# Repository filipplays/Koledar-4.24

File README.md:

# Koledar 4.24 <br /> _The customizable birthday calendar_

---

This is my attempt at making a simple calendar for the elderly. It displays the date, time, and up to three birthdays at a time. It was made with the intention that a caretaker would input up to 146 birthdays to the Koledar hardware with the Koledar GUI and take the device to the person's home, where it just needs to be powered next to a window.
<br/> The device uses GPS to read the date and time which makes it completely autonomous.
<br/> The project was made to help my grandma stay as independent as possible by helping her with attending appointments, watching TV shows, and remembering birthdays. It took some getting used to but she says that it is helpful.
<br/> The project started as an extra assignment in the first year of my bachelor's degree in electrical engineering, and it has now been updated two times.

## The creation of the project

### Hardware

The only thing I designed myself was the connector PCB. It neatly fits into the casing and connects the GPS module, display, and Arduino.

I used the [NEO-6M GPS module](https://randomnerdtutorials.com/guide-to-neo-6m-gps-module-with-arduino/) for connectivity because it is very well supported on Arduino. The screen is a [5'' touch screen from DIY more](https://www.diymore.cc/products/5-0-800x480-tft-lcd-module-display-touch-panel-ssd1963-for-51-avr-stm32/) with a resolution of 800x480px. I know which library to use with it since I have used it in the previous version and I didn't have any problems with it, so I just used it again. [This](http://rinkydinkelectronics.com/library.php?id=51) is the LCD library. I used a knockoff [Arduino MEGA 2560](https://store.arduino.cc/en-si/products/arduino-mega-2560-rev3?srsltid=AfmBOopCFWO4uVFIkQQ2IXemMtiKCIKrwHhKWaTtJ1ZzTIYdNrtdq98T) board. I didn't put a lot of thought into the board selection. I used an Arduino for all of the previous versions and since the only necessity was enough pins to drive the display and communicate with the GPS module, and the MCU didn't have to be fast or feature-rich, I stuck with the Arduino. For the next iteration, I will consider other platforms.
<br> Altogether the hardware for the latest version costs approx. 70€, and it was all bought from AliExpress.

### Case

The wooden case was made by my [dad](https://www.instagram.com/bybojci/). He used a laser cutter and thin pieces of wood to complete the construction. Since we only made a couple of these systems we made sure that the final product looked and felt pleasing.

### Firmware

I wrote all of the firmware excluding the LCD and GPS libraries and the code in the "byDay_of_week" function. That code was taken from the internet in my first year but I can't find the source.
<br/> The emphasis when writing the FW was readability and maintainability. I decided to try to use a version of the Hungarian notation, commented all of the code in Doxy style, and used it to generate the documentation. I found the style pleasant but unnecessary at times. I feel like the Doxygen-generated documentation will be useful when coming back to the project at a later time.

<center></center>

<br/> The FW needs to handle getting the time and date from GPS and displaying the appropriate data. When the GUI connects to the HW over USB it also needs to handle the communication, writing, and reading from the EEPROM. In the case that the GPS signal is lost the system displays small text in the bottom left corner indicating that the date and time functionality is being powered from the internal Arduino clock. This is not ideal as the timer is not accurate at all, but for a short time while the GPS signal is not available it's fine.
<br/> The screen used to go black during the night but it was still somewhat bright because of the backlight. I scratched the trace used for powering the LCD backlight in half and sodered a transistor I had in between the connections. I used a free Arduino PWM-enabled GPIO to drive the LCD brightness which enabled me to completely turn it off or dim it.
<br/> The fonts from the [LCD library](http://rinkydinkelectronics.com/library.php?id=51) didn't work well for me so I decided to make my own. I made a simple website that enabled me to draw the letters in a 10 by 12 grid and copy the unsigned integer array to put into a header file. This way I could quickly iterate over different designs and add Slovenian characters that aren't in the English alphabet.

<center>

</center>

## GUI

<center>

</center>

I wanted anyone to be able to set up the Koledar so I made the Koledar GUI. It is a Windows application written in Python using Tkinter. Its main functionality is to enable the user to read and write birthdays to the system, but it can also change the text and background color and change the default brightness of the screen.
<br/> The improvement from the previous version was focused on the user experience. I added an alert box when the user attempts to delete the birthdays and the theme profile. I also changed the button layout in a way that makes more sense.

<center>

</center>

## Known issues

- With certain combinations of colors and brightness the screen starts displaying an effect similar to when a screen is recorded and the shutters aren't in sync.
- The upload of all 146 birthdays takes approx. 15 seconds. At this time the Koledar GUI is unresponsive.
- The user is unable to write the letter 'č' in the Koledar GUI, so they have to copy it from another editor and paste it in.
- Birthdays with names longer than ~19 characters (depending on the birthday date) are very small on the display.

## Future Improvements

The main feature I would change is the way in which the system tracks the time. I initially chose GPS when the system didn't have the ability to store and display birthdays because I wanted it to be plug-and-play. Meaning that I just brought it to where I wanted it (and near a window) and powered it. It also meant that anytime the system was reset it didn't need any input from the user.
<br> For future versions I would use an accurate RTC IC with a coin battery backup, like [this](https://eu.mouser.com/ProductDetail/NXP-Semiconductors/PCF2131TFY?qs=QNEnbhJQKvbnVL67jlWDOg%3D%3D). Since the user needs to upload the birthdays the system needs to be connected to a PC at least once, where it could read the date and time or let the user input their own. These systems also take care of the calendar logic. This would have the advantage of not having to place the Koledar next to a window, and once it was in sync it wouldn't have to wait for any signal if it was reset.
<br> I could also make use of the longwave time signal stations like [DCF77](https://en.wikipedia.org/wiki/DCF77). This could be used for a separate system that doesn't need the birthday functionality so it would never get connected to a PC to set the time.

<br> Another interesting thing to change would be the MCU. In this context, I think there is nothing wrong with using an Arduino, but using something like an ESP32 devkit or a custom PCB could be interesting for the connectivity. I'm just not sure what I would use it for... yet!

<br> The screen was the most expensive part of the build and I think I can do the build for cheaper. It's nice that it is a touch-capable display so that when the screen is turned off you can briefly turn it on when you touch it, but I could also add a small button to the case for that, and maybe other controls as well. It might also make for a good tactile addition.

<br> I might do an E-INK, battery-powered, cordless Koledar at some point too.

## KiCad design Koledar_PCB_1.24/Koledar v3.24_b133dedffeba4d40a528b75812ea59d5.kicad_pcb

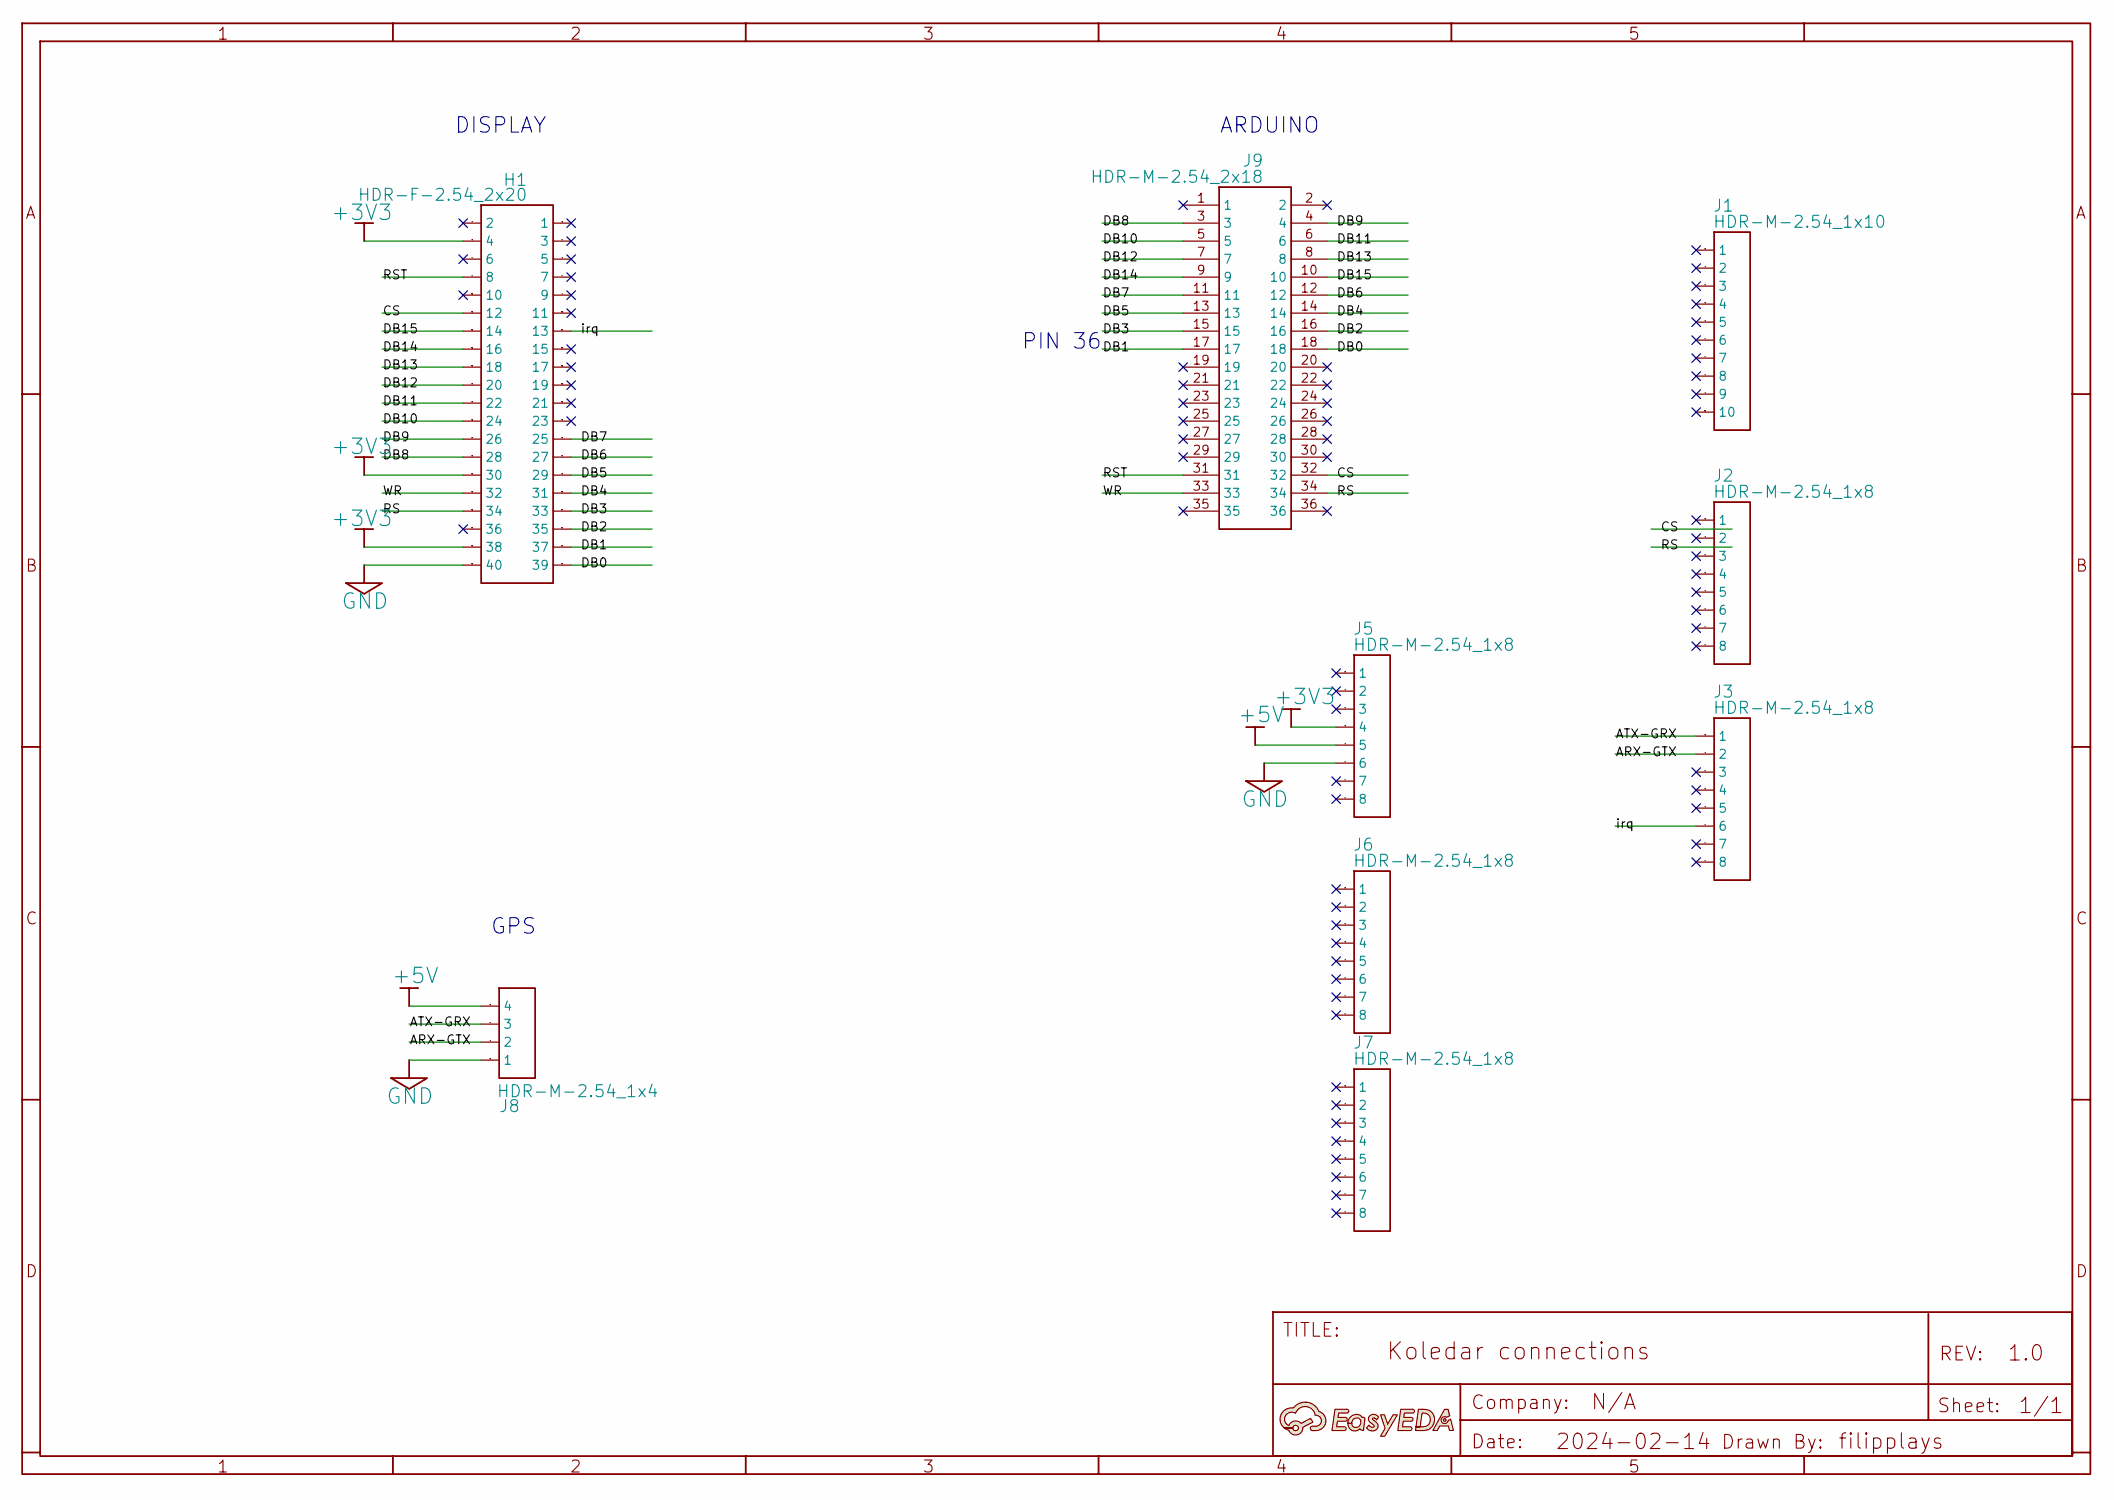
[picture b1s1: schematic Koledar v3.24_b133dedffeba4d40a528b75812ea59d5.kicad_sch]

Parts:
A: A; Manufacturer Part ?
H1: HDR-F-2.54_2x20
J1: HDR-M-2.54_1x10
J2, J3, J5, J6, J7: HDR-M-2.54_1x8
J8: HDR-M-2.54_1x4
J9: HDR-M-2.54_2x18

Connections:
+3V3: H1.4, H1.30, H1.38, J5.4
+5V: J5.5, J8.4
ARX-GTX: J3.2, J8.2
ATX-GRX: J3.1, J8.3
CS: H1.12, J9.32
DB0: H1.39, J9.18
DB1: H1.37, J9.17
DB2: H1.35, J9.16
DB3: H1.33, J9.15
DB4: H1.31, J9.14
DB5: H1.29, J9.13
DB6: H1.27, J9.12
DB7: H1.25, J9.11
DB8: H1.28, J9.3
DB9: H1.26, J9.4
DB10: H1.24, J9.5
DB11: H1.22, J9.6
DB12: H1.20, J9.7
DB13: H1.18, J9.8
DB14: H1.16, J9.9
DB15: H1.14, J9.10
GND: H1.40, J5.6, J8.1
IRQ: H1.13, J3.6
RS: H1.34, J9.34
RST: H1.8, J9.31
WR: H1.32, J9.33

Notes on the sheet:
DISPLAY
ARDUINO
PIN 36
GPS

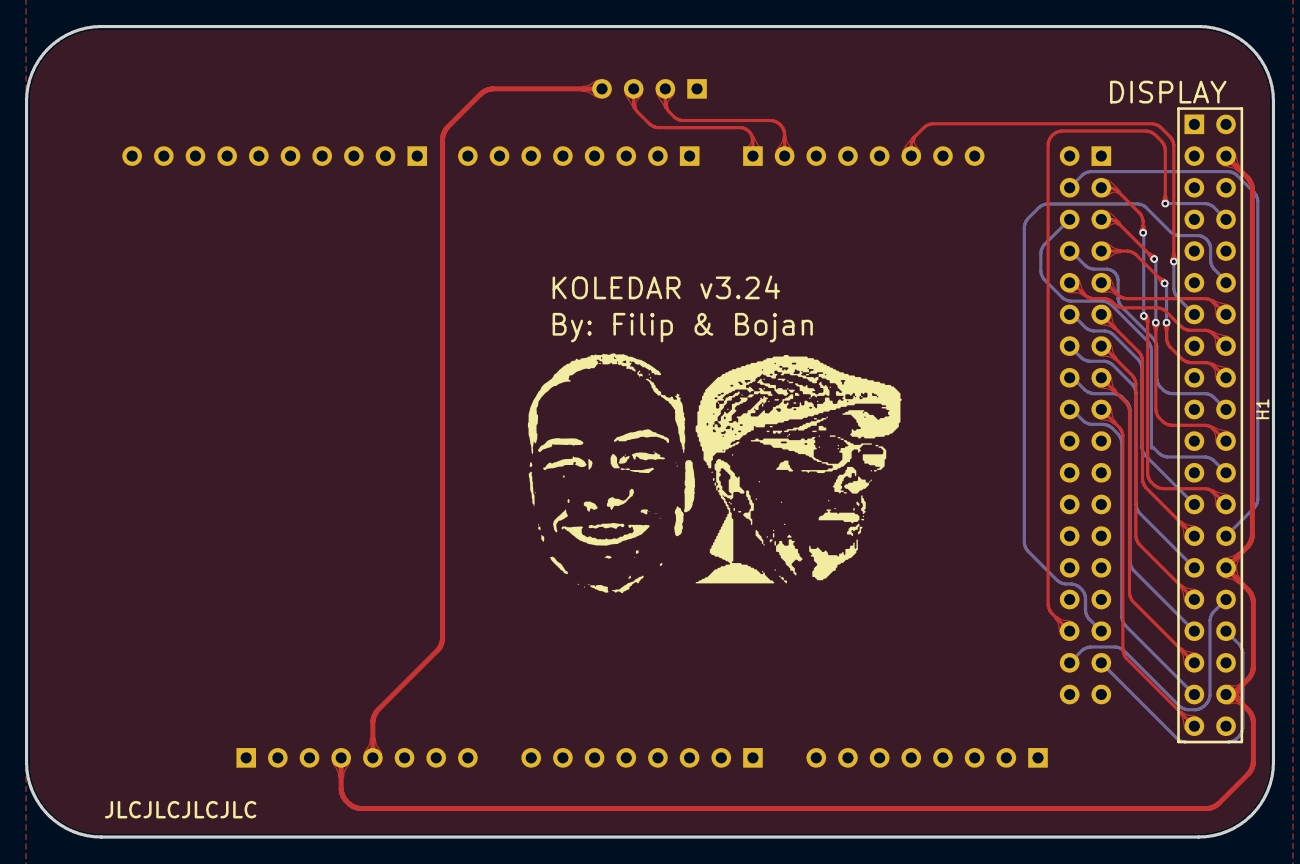
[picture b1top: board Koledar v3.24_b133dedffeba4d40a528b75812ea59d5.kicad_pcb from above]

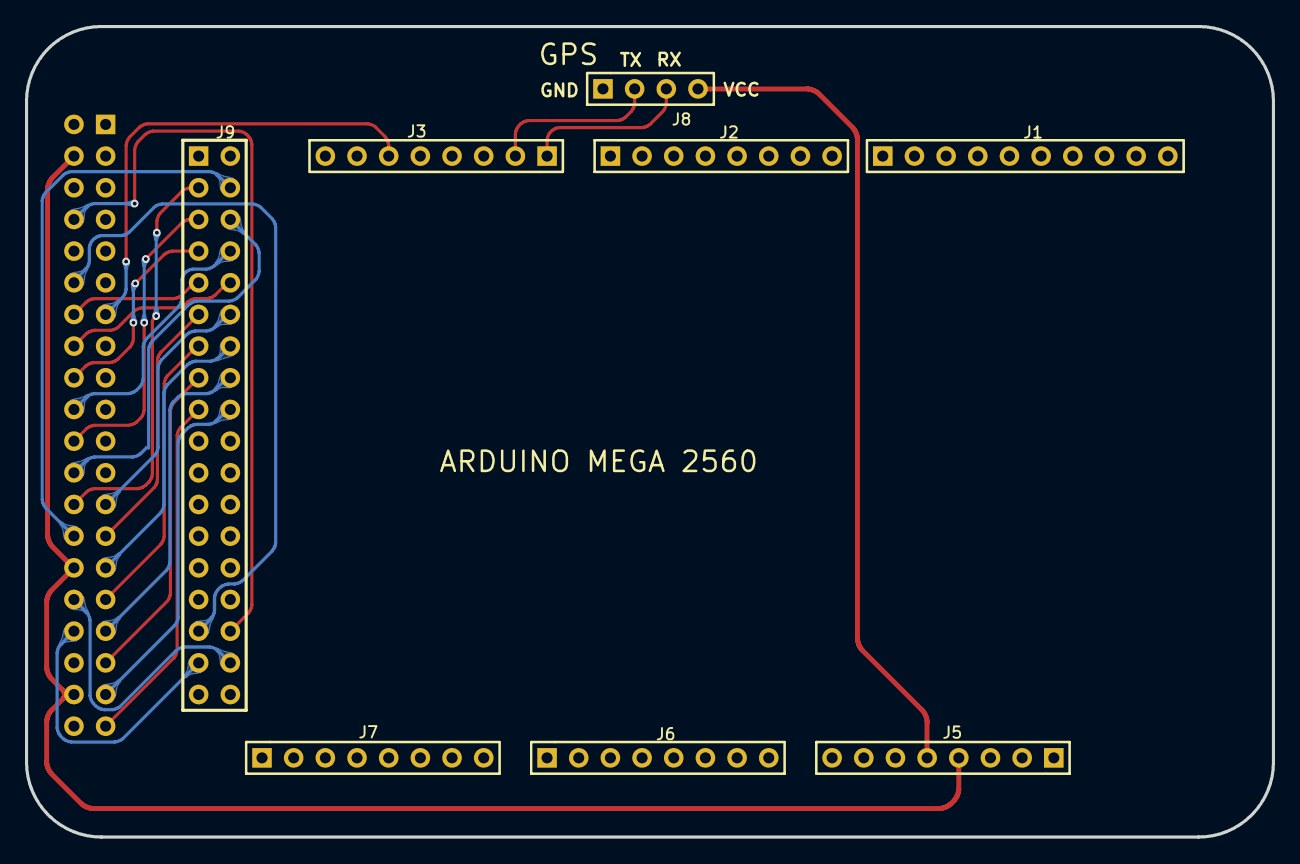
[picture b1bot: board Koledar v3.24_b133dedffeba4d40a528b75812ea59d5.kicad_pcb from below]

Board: 2 copper layers, 100.0 x 65.0 mm, 9 parts (8 on the bottom side), 26 nets.

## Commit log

2024-10-16 REAME and repo languages FIX
2025-01-25 Bug fix and code improvement
    Fixed the zero days in February bug. Changed the code style in BD.h/.c, kept the functionality the same. Changed the character constant arrays for i and j to "_i" and "_j" to remove shadowing variabl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
2025-01-25 Remove mistake from prev commit.
    Remove BD::
2025-04-02 Fixed bug and added .gitignore
    Fixed bug where if a person was 4 years old an out of bounds array read would happen. Also added .gitignore for ignoring the backups folder of the PCB folder.
